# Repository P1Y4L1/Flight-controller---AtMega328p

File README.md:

# Flight-controller---AtMega328p
PCB designs of a flight controller with the help of AtMega328p

Flight controls nowadays are costly and are too complex to operate for a beginner with drones. 
This makes operating the drone difficult and also we  consider the fact that we need to buy the expensive flight controller from the market. 
The significance of this paper is to show that we can make a basic flight controller back at home making it cheap and also quite basic to operate.
The 3 softwares used to make the PCB design of the Flight controller is Eagle Cad which is quite famous in the market however it is highly charged ;  
KiCad , a free and an open source software which is easily accessible and is beginner friendly ; last but not the least Fritzing , which is not commonly used by 
everyone , but is also open source but makes electronics accessible as a creative material for anyone.  With the help of these 3 softwares , it is shown that the 
PCB design of the Flight controller can be made in any software required and not necessarily in any of those 3 mentioned above.

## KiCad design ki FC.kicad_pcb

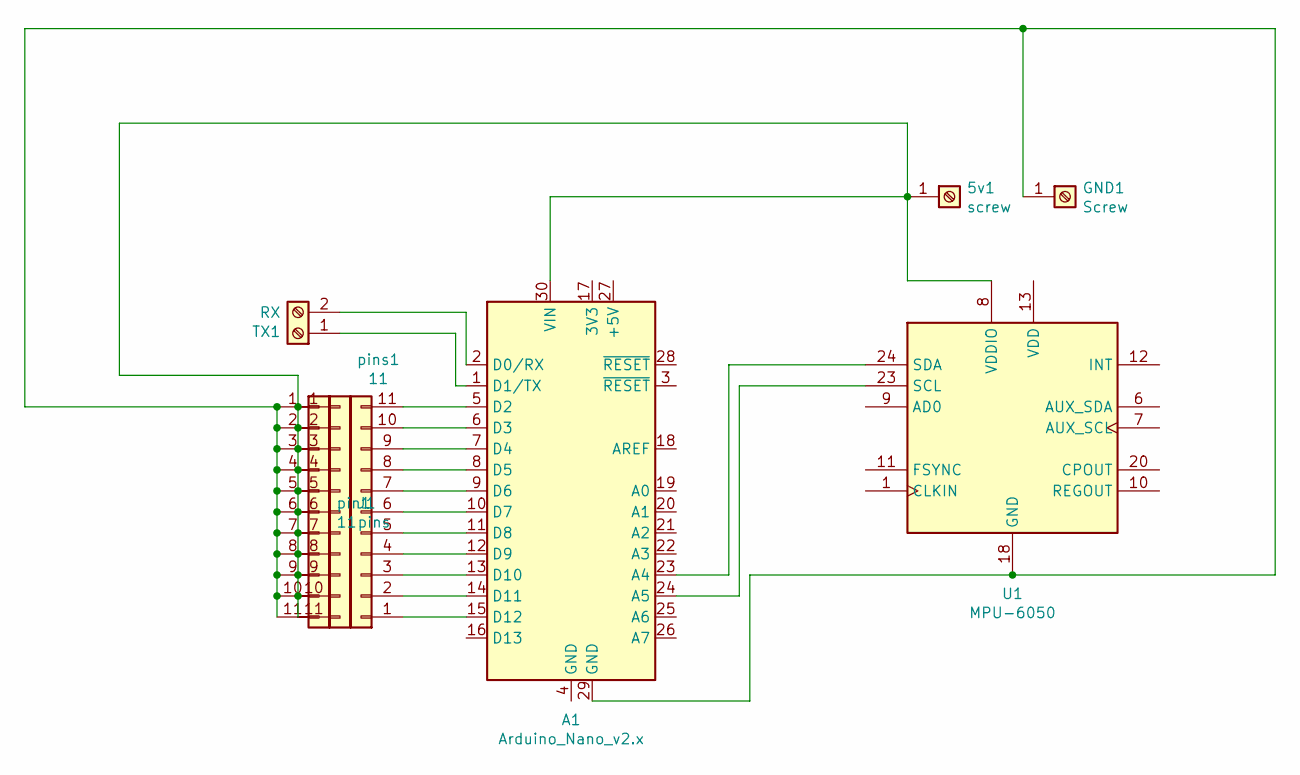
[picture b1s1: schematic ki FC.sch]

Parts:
5v1: screw; TerminalBlock_MetzConnect_360322_1x01_Horizontal_ScrewM3.0_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
A1: Arduino_Nano_v2.x; Arduino_Nano
GND1: Screw; TerminalBlock_MetzConnect_360291_1x01_Horizontal_ScrewM3.0_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
J1: pins; Stocko_MKS_1661-6-0-1111_1x11_P2.50mm_Vertical
TX1: RX; TerminalBlock_Phoenix_PT-1,5-2-5.0-H_1x02_P5.00mm_Horizontal
U1: MPU-6050; InvenSense_QFN-24_4x4mm_P0.5mm
pin1: 11; Stocko_MKS_1661-6-0-1111_1x11_P2.50mm_Vertical
pins1: 11; Stocko_MKS_1661-6-0-1111_1x11_P2.50mm_Vertical

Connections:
unnamed: 5v1.1, A1.30 (VIN), J1.1, J1.2, J1.3, J1.4, J1.5, J1.6, J1.7, J1.8, J1.9, J1.10, J1.11, U1.8 (VDDIO)
unnamed: A1.1 (D1/TX), TX1.1
unnamed: A1.2 (D0/RX), TX1.2
unnamed: A1.5 (D2), pins1.11
unnamed: A1.6 (D3), pins1.10
unnamed: A1.7 (D4), pins1.9
unnamed: A1.8 (D5), pins1.8
unnamed: A1.9 (D6), pins1.7
unnamed: A1.10 (D7), pins1.6
unnamed: A1.11 (D8), pins1.5
unnamed: A1.12 (D9), pins1.4
unnamed: A1.13 (D10), pins1.3
unnamed: A1.14 (D11), pins1.2
unnamed: A1.15 (D12), pins1.1
unnamed: A1.23 (A4), U1.24 (SDA)
unnamed: A1.24 (A5), U1.23 (SCL)
unnamed: A1.29 (GND), GND1.1, U1.18 (GND), pin1.1, pin1.2, pin1.3, pin1.4, pin1.5, pin1.6, pin1.7, pin1.8, pin1.9, pin1.10, pin1.11

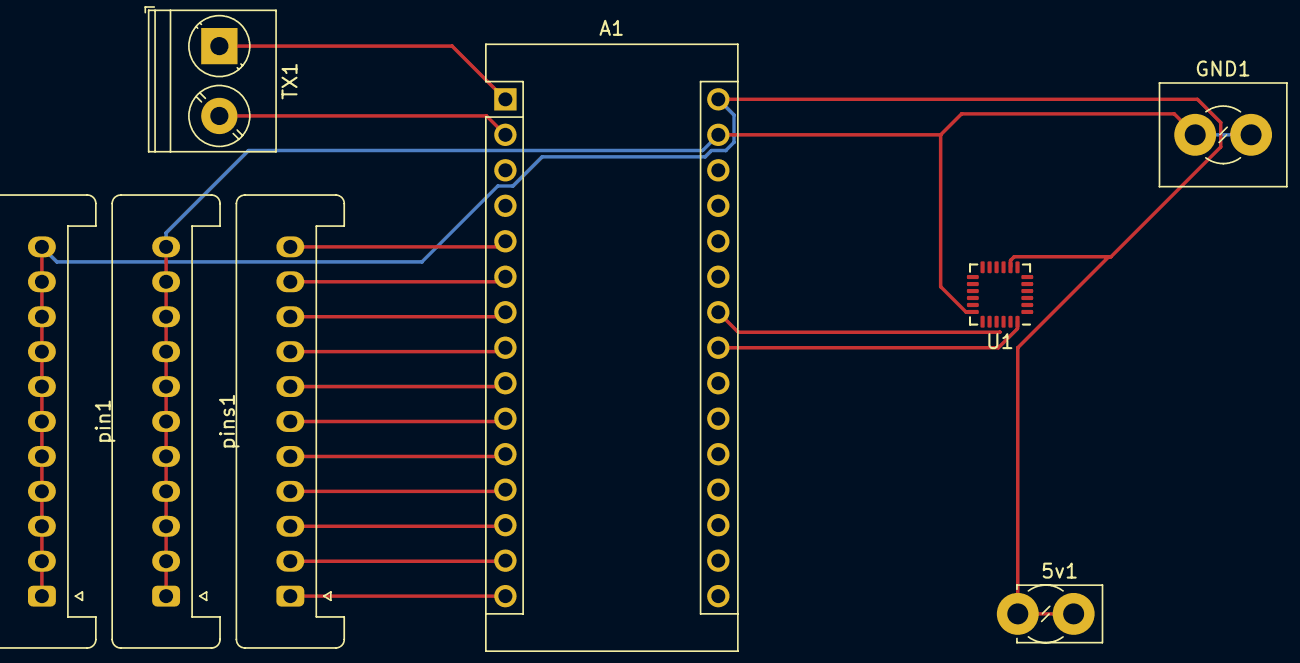
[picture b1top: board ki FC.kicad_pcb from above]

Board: 2 copper layers, 8 parts (0 on the bottom side), 17 nets.

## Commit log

2021-02-18 PCB designs of a flight controller with the help of AtMega328p
    files uploaded of pro. ; sch. ; brd. file types
